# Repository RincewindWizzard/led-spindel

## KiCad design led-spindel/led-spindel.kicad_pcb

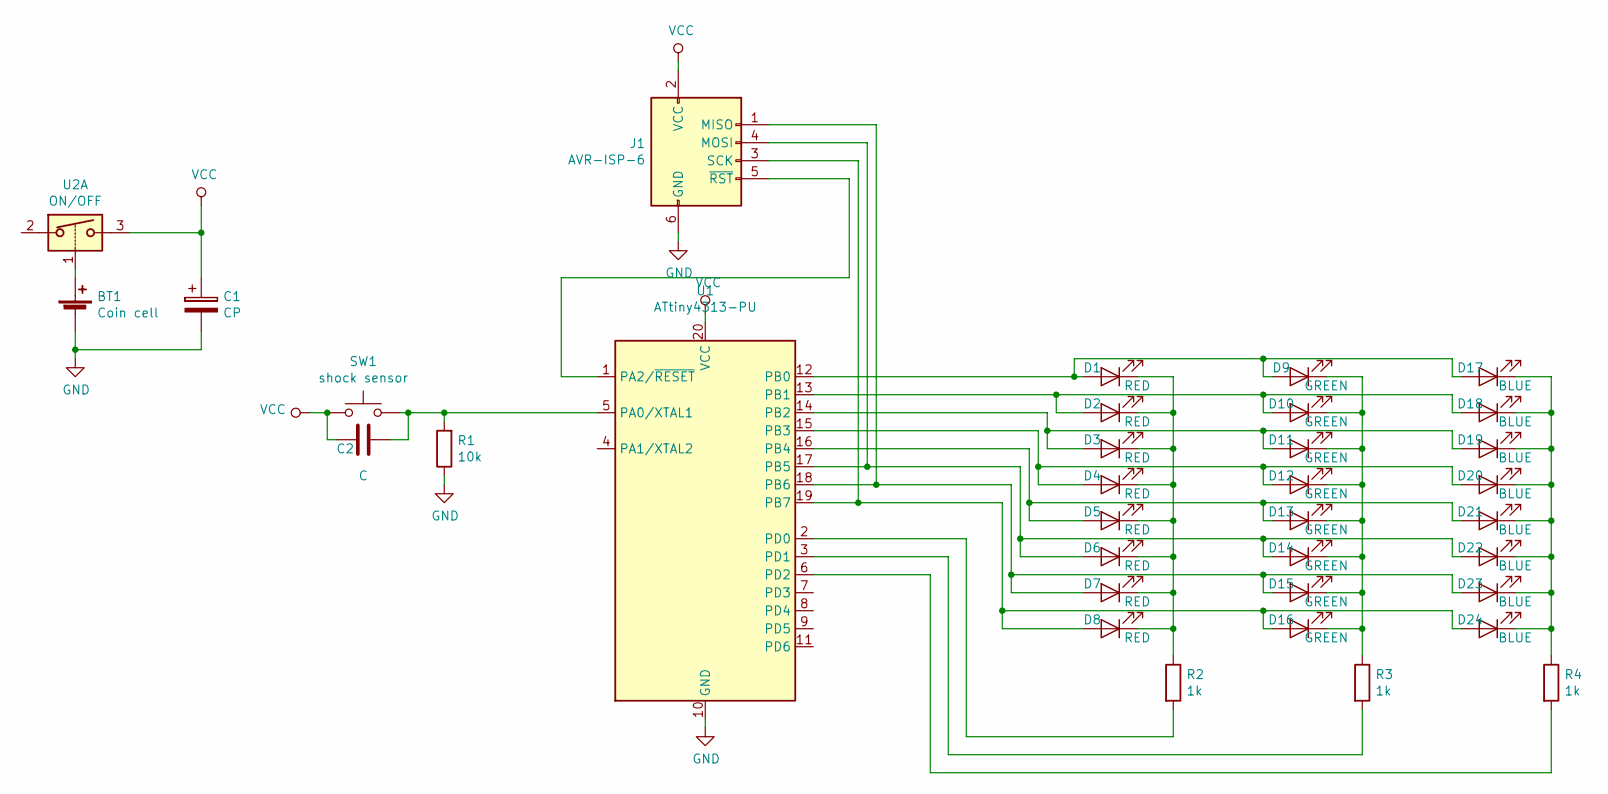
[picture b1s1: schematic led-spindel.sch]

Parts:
BT1: Coin cell; CH224-2032
C1: CP; CP_Radial_D6.3mm_P2.50mm
C2: C; C_Disc_D3.0mm_W1.6mm_P2.50mm
D1, D2, D3, D4, D5, D6, D7, D8: RED; LED_D3.0mm
D9, D10, D11, D12, D13, D14, D15, D16: GREEN; LED_D3.0mm
D17, D18, D19, D20, D21, D22, D23, D24: BLUE; LED_D3.0mm
J1: AVR-ISP-6; ISP6-Header
R1: 10k; Resistor
R2, R3, R4: 1k; Resistor
SW1: shock sensor; SW-18020
U1: ATtiny4313-PU; attiny4313
U2: ON/OFF; Switch

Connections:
GND: BT1.2 (-), C1.2, J1.6 (GND), R1.1, U1.10 (GND)
unnamed: BT1.1 (+), U2.1
unnamed: C2.2, R1.2, SW1.2, U1.5 (PA0/XTAL1)
unnamed: D1.1 (K), D2.1 (K), D3.1 (K), D4.1 (K), D5.1 (K), D6.1 (K), D7.1 (K), D8.1 (K), R2.1
unnamed: D1.2 (A), D9.2 (A), D17.2 (A), U1.12 (PB0)
unnamed: D9.1 (K), D10.1 (K), D11.1 (K), D12.1 (K), D13.1 (K), D14.1 (K), D15.1 (K), D16.1 (K), R3.1
unnamed: D2.2 (A), D10.2 (A), D18.2 (A), U1.13 (PB1)
unnamed: D3.2 (A), D11.2 (A), D19.2 (A), U1.14 (PB2)
unnamed: D4.2 (A), D12.2 (A), D20.2 (A), U1.15 (PB3)
unnamed: D5.2 (A), D13.2 (A), D21.2 (A), U1.16 (PB4)
unnamed: D6.2 (A), D14.2 (A), D22.2 (A), J1.4 (MOSI), U1.17 (PB5)
unnamed: D7.2 (A), D15.2 (A), D23.2 (A), J1.1 (MISO), U1.18 (PB6)
unnamed: D8.2 (A), D16.2 (A), D24.2 (A), J1.3 (SCK), U1.19 (PB7)
unnamed: D17.1 (K), D18.1 (K), D19.1 (K), D20.1 (K), D21.1 (K), D22.1 (K), D23.1 (K), D24.1 (K), R4.1
unnamed: J1.5 (~RST), U1.1 (PA2/~RESET)
unnamed: R2.2, U1.2 (PD0)
unnamed: R3.2, U1.3 (PD1)
unnamed: R4.2, U1.6 (PD2)
VCC: C1.1, C2.1, J1.2 (VCC), SW1.1, U1.20 (VCC), U2.3

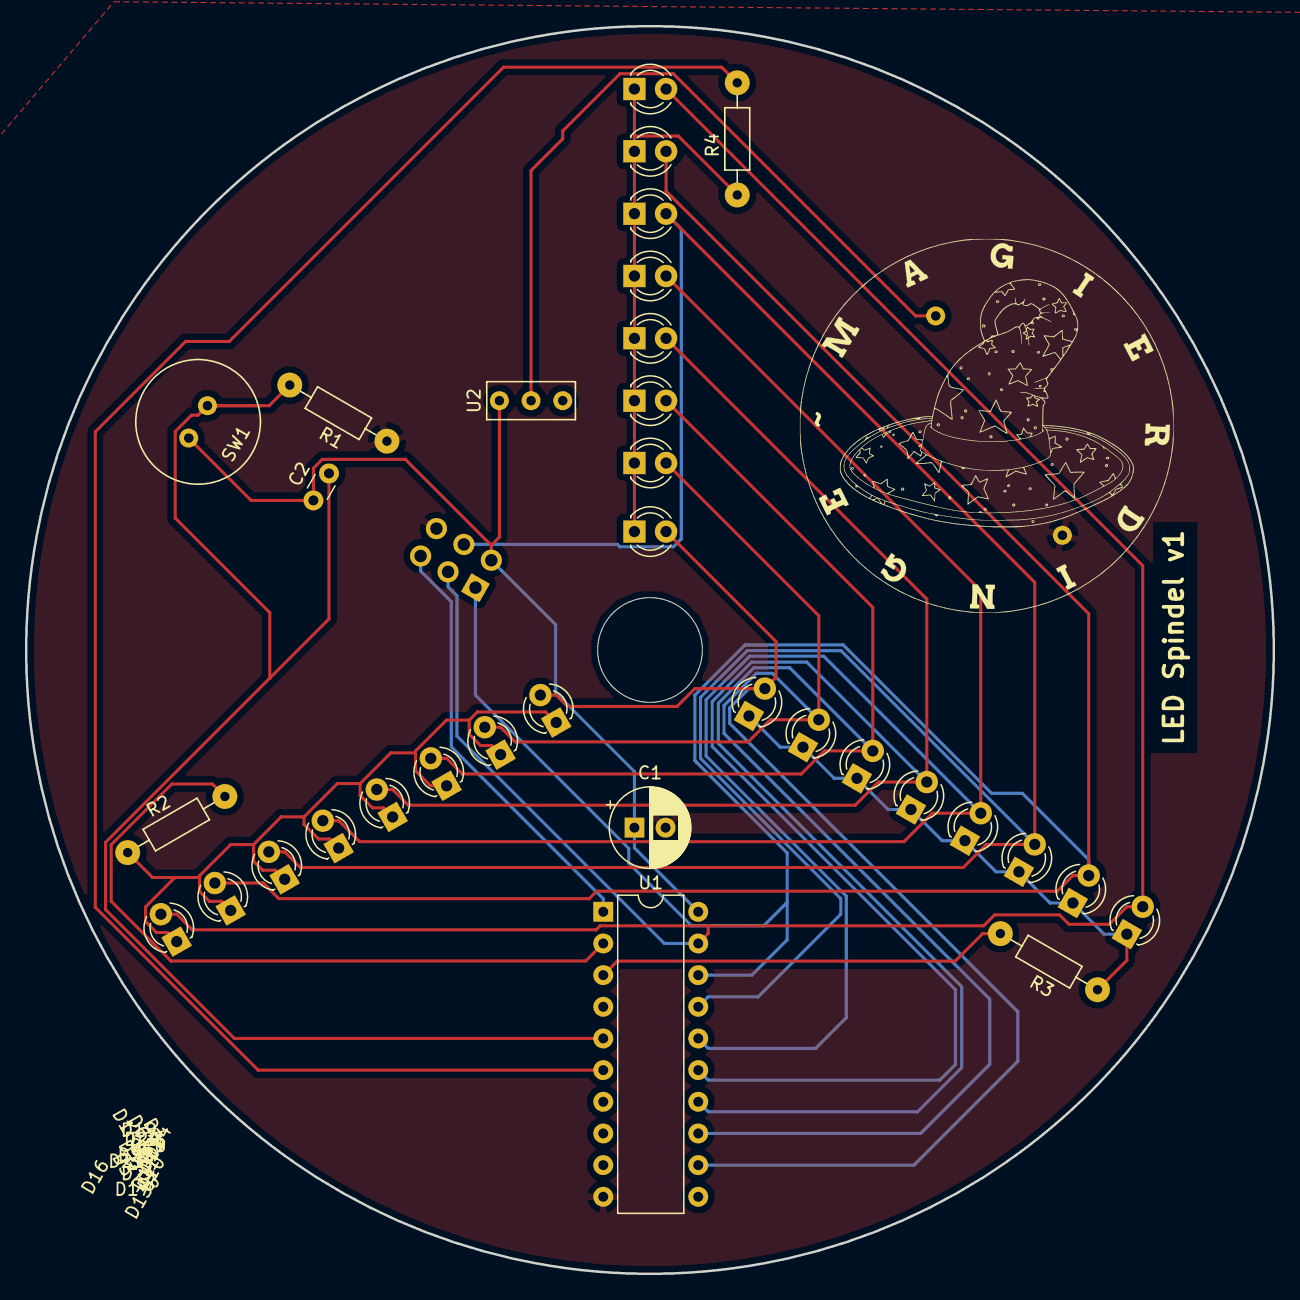
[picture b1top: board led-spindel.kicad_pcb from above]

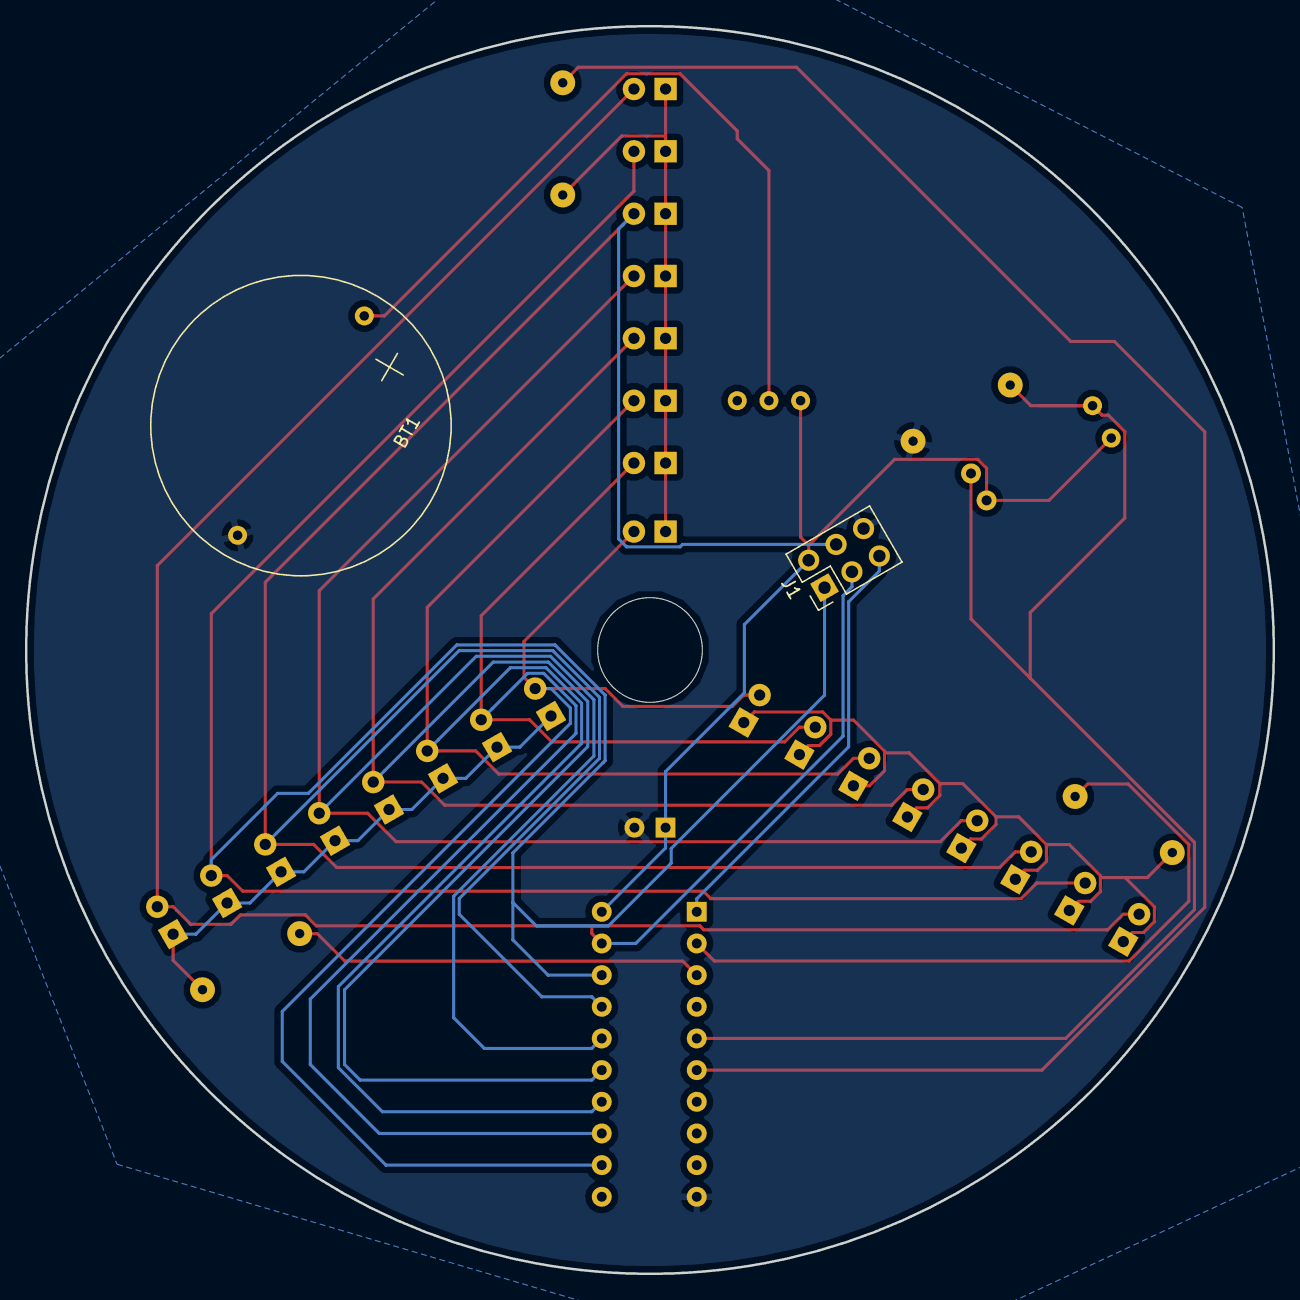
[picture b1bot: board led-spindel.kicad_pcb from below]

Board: 2 copper layers, 100.1 x 100.1 mm, 35 parts (2 on the bottom side), 19 nets.
